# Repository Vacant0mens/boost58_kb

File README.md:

# boost58_kb
 
This layout was given this name because its shape looks similar to the boost arrows in racetrack video games.

# Introduction
I designed this board because I couldn't find any options that fit my requirements for a custom key board, which were:
1. completely reversible circuit board (for a split keyboard)
2. two-way UART communication between the two halves
3. compatible with Kailh Choch v2 switches (with v1 backward compatability)
4. hotswap switch sockets
5. staggered column layout (including a stagger for the outer-pinky column, and inner-index column)
6. 4 finger rows, plus only one thumb row
7. per-key and underglow RGB lights
8. anti-ghosting diodes
9.  promicro-style MCU
10. at least 1 rotary encoder per-side
11. reset button
12. power switch (optional)

I designed this with the intention of making it my dream keyboard, but also available and accessible to others. I am open to suggestions and PR's.

# Build Progress

## v0.2
### Top Layout v0.2

## v0.1

### Original Top Layout

# Thanks
Thanks to:
[ergogen](https://github.com/ergogen/ergogen) for the base software to be able to create this.
[ceoloide](https://github.com/ceoloide/ergogen-footprints) for the footprints and examples
[benvallack](https://github.com/benvallack) for the inspiration that started my custom keyboard journey and the `promicro_pretty` footprint (it's amazing).

# Buy Me a Coffee
[@Vacant0mens](https://buymeacoffee.com/vacan0mens)

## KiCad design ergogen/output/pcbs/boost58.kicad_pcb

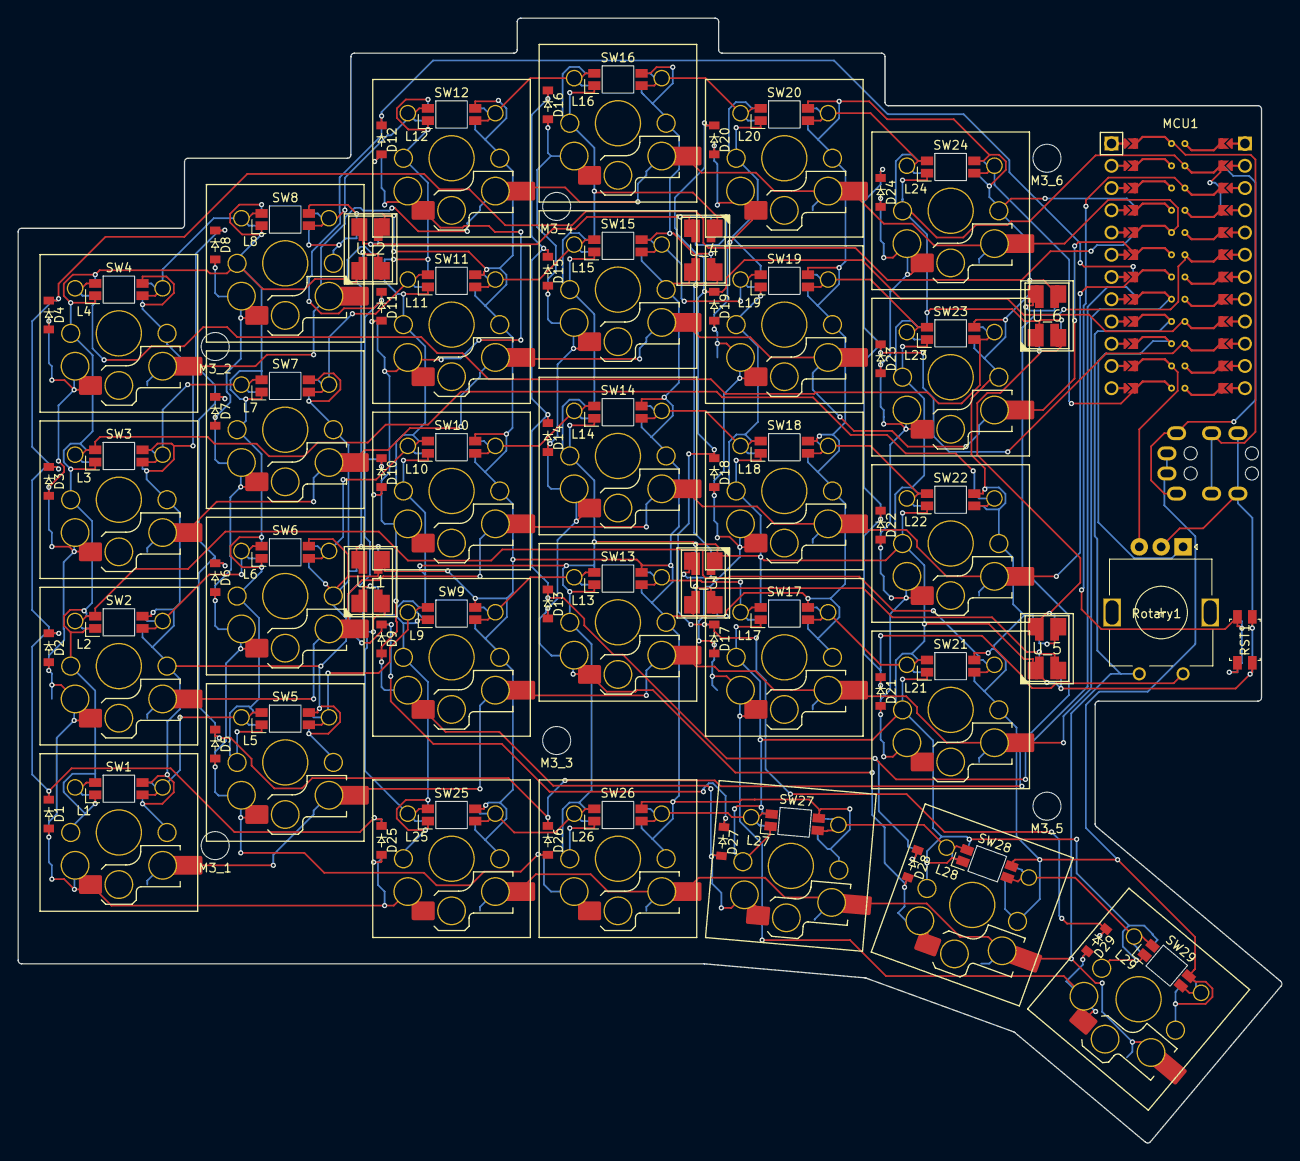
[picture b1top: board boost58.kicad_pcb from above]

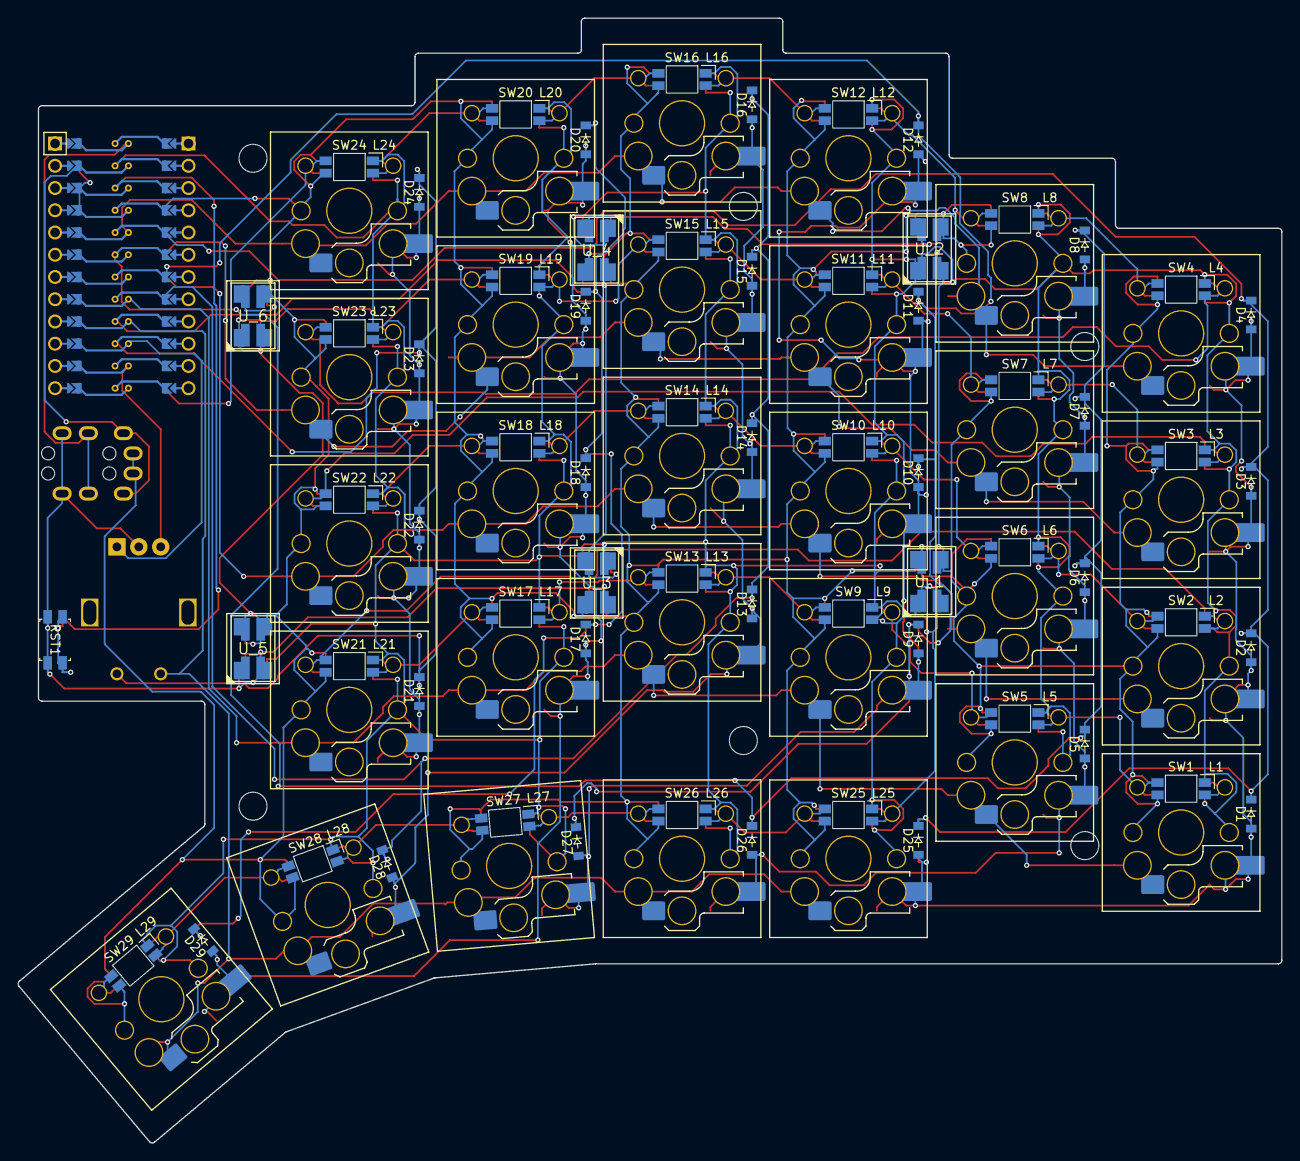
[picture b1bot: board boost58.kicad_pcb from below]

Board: 2 copper layers, 144.3 x 128.5 mm, 103 parts (87 on the bottom side), 59 nets.

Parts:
D1, D2, D3, D4, D5, D6, D7, D8, D9, D10, D11, D12, D13, D14, D15, D16, D17, D18, D19, D20, D21, D22, D23, D24, D25, D26, D27, D28, D29: ${REFERENCE}; diode_tht_sod123
L1, L2, L3, L4, L5, L6, L7, L8, L9, L10, L11, L12, L13, L14, L15, L16, L17, L18, L19, L20, L21, L22, L23, L24, L25, L26, L27, L28, L29: ${REFERENCE}; led_SK6812mini-e (per-key, reversible)
M3_1, M3_2, M3_3, M3_4, M3_5, M3_6: mounting_hole_npth
MCU1: ProMicro
RST1: reset_switch_smd_side
Rotary1: rotary_encoder
SW1, SW2, SW3, SW4, SW5, SW6, SW7, SW8, SW9, SW10, SW11, SW12, SW13, SW14, SW15, SW16, SW17, SW18, SW19, SW20, SW21, SW22, SW23, SW24, SW25, SW26, SW27, SW28, SW29: ${REFERENCE}; switch_choc_v1_v2
TRRS1: TRRS-PJ-320A-dual
U_1, U_2, U_3, U_4, U_5, U_6: ${REFERENCE}; WS2812B

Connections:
DP14: D21.2, D22.2, D23.2, D24.2, SW21.2, SW22.2, SW23.2, SW24.2
DP15: D17.2, D18.2, D19.2, D20.2, D29.2, SW17.2, SW18.2, SW19.2, SW20.2, SW29.2
DP18: D13.2, D14.2, D15.2, D16.2, D28.2, SW13.2, SW14.2, SW15.2, SW16.2, SW28.2
DP19: D9.2, D10.2, D11.2, D12.2, D27.2, SW9.2, SW10.2, SW11.2, SW12.2, SW27.2
DP20: D5.2, D6.2, D7.2, D8.2, D26.2, SW5.2, SW6.2, SW7.2, SW8.2, SW26.2
DP21: D1.2, D2.2, D3.2, D4.2, D25.2, SW1.2, SW2.2, SW3.2, SW4.2, SW25.2
GND: L1.3, L2.3, L3.3, L4.3, L5.3, L6.3, L7.3, L8.3, L9.3, L10.3, L11.3, L12.3, L13.3, L14.3, L15.3, L16.3, L17.3, L18.3, L19.3, L20.3, L21.3, L22.3, L23.3, L24.3, L25.3, L26.3, L27.3, L28.3, L29.3, MCU1.2, MCU1.21, MCU1.22, RST1.1, RST1.3, Rotary1.C, TRRS1.4, U_1.3, U_1.4, U_1.33, U_1.44, U_2.3, U_2.4, U_2.33, U_2.44, U_3.3, U_3.4, U_3.33, U_3.44, U_4.3, U_4.4, U_4.33, U_4.44, U_5.3, U_5.4, U_5.33, U_5.44, U_6.3, U_6.4, U_6.33, U_6.44
P0: MCU1.23, TRRS1.2
P1: MCU1.24, TRRS1.3
P2: MCU1.20, SW4.1, SW8.1, SW12.1, SW16.1, SW20.1, SW24.1
P3: MCU1.19, SW3.1, SW7.1, SW11.1, SW15.1, SW19.1, SW23.1
P4: MCU1.18, SW2.1, SW6.1, SW10.1, SW14.1, SW18.1, SW22.1
P5: MCU1.17, SW1.1, SW5.1, SW9.1, SW13.1, SW17.1, SW21.1
P6: MCU1.16, Rotary1.2, SW25.1, SW26.1, SW27.1, SW28.1, SW29.1
P7: MCU1.15, Rotary1.A
P8: MCU1.14, Rotary1.B
P9: L24.2, MCU1.13
P14: D21.1, D22.1, D23.1, D24.1, MCU1.10, Rotary1.1
P15: D17.1, D18.1, D19.1, D20.1, D29.1, MCU1.9
P18: D13.1, D14.1, D15.1, D16.1, D28.1, MCU1.8
P19: D9.1, D10.1, D11.1, D12.1, D27.1, MCU1.7
P20: D5.1, D6.1, D7.1, D8.1, D26.1, MCU1.6
P21: D1.1, D2.1, D3.1, D4.1, D25.1, MCU1.5
RST: MCU1.3, RST1.2, RST1.4
VCC: L1.1, L2.1, L3.1, L4.1, L5.1, L6.1, L7.1, L8.1, L9.1, L10.1, L11.1, L12.1, L13.1, L14.1, L15.1, L16.1, L17.1, L18.1, L19.1, L20.1, L21.1, L22.1, L23.1, L24.1, L25.1, L26.1, L27.1, L28.1, L29.1, MCU1.4, TRRS1.1, U_1.1, U_1.2, U_1.11, U_1.22, U_2.1, U_2.2, U_2.11, U_2.22, U_3.1, U_3.2, U_3.11, U_3.22, U_4.1, U_4.2, U_4.11, U_4.22, U_5.1, U_5.2, U_5.11, U_5.22, U_6.1, U_6.2, U_6.11, U_6.22
r0c1: L25.4, U_1.3, U_1.4, U_1.33, U_1.44
r0c2: L25.2, L26.4
r0c3: L26.2, L27.4
r0c4: L27.2, L28.4
r0c5: L28.2, L29.4
r1c1: L1.2, L5.4
r1c2: L5.2, L9.4
r1c3: L9.2, L13.4
r1c4: L13.2, L17.4
r1c5: L17.2, L21.4
r2c0: L2.4, L21.2
r2c1: L2.2, L6.4
r2c2: L6.2, L10.4
r2c3: L10.2, L14.4
r2c4: L14.2, L18.4
r2c5: L18.2, L22.4
r3c0: L3.4, L22.2
r3c1: L3.2, L7.4
r3c2: L7.2, L11.4
r3c3: L11.2, L15.4
r3c4: L15.2, L19.4
r3c5: L19.2, L23.4
r4c0: L4.4, L23.2
r4c1: L4.2, L8.4
r4c2: L8.2, L12.4
r4c3: L12.2, L16.4
r4c4: L16.2, L20.4
r4c5: L20.2, L24.4
u01: U_1.1, U_1.2, U_1.11, U_1.22, U_2.3, U_2.4, U_2.33, U_2.44
u02: U_2.1, U_2.2, U_2.11, U_2.22, U_4.3, U_4.4, U_4.33, U_4.44
u03: U_3.3, U_3.4, U_3.33, U_3.44, U_4.1, U_4.2, U_4.11, U_4.22
u04: U_3.1, U_3.2, U_3.11, U_3.22, U_5.3, U_5.4, U_5.33, U_5.44
u05: U_5.1, U_5.2, U_5.11, U_5.22, U_6.3, U_6.4, U_6.33, U_6.44
u06: U_6.1, U_6.2, U_6.11, U_6.22

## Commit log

2024-08-11 Initialized repo with Readme
2024-08-11 created ergogen config yaml
2024-08-11 pulled and modified footprints from ceoloide's footprints repo (PR incoming later)
2024-08-11 generated KiCad PCB's and outlines with ergogen
2024-08-11 autorouted and imported session to PCB
2024-08-11 exported STEP files for bottom, top, and spacer plates, and converted them to STL's for printing
2024-08-11 generated gerber and drill files (and put them in zip files for later use)
2024-08-11 updated ergogen config to have correct name in output files
2024-08-11 added picture of layout
2024-08-11 renamed files to correct name instead of generic/prototype name
2024-08-17 forgot to update the name when adding meta section
2024-08-20 reduced binding around inner_home key
2024-08-20 removed commented lines, refactored outline references to short syntax, made panel and keycap_outline internal-only
2024-08-20 removed PCB plates in favor of using the outlines as sketches in Fusion to make the case
2024-08-20 added keycap outlines to pcb silkscreens
2024-08-20 added a wall outline for the wall of the bottom case
2024-08-20 added material around the screw holes to support PCB
2024-08-20 increased _switch_spacer_cutouts size for better printability
2024-08-20 changed screw posts to be bigger, for heat-set threaded inserts
2024-08-20 changed size of top_plate cutout for MCU and Rotary Encoder
2024-08-20 created v0.1 zip file - main PCB has been made from these files
2024-08-20 removed excess outline and pcb files (already removed from config.yml)
2024-08-20 re-generated files for drawings (to make a new case in Fusion)
2024-08-20 un-did changes to top-plate cutout and binding on inner home key (will be part of v0.2 branch)
2024-08-20 reduced binding around inner_home and moved PowerSwitch to make pcb and case more streamlined
2024-08-20 moved screw holes and LED's for better placement with heat insert threads and bigger notch above thumb_inner
2024-08-20 re-generated PCB and drawings (will run auto-trace later)
2024-08-20 moved power switch back to match v0.1 until v0.2 is ready for PCB creation and new case
2024-08-20 added polygon to MCU/Rotary cutout so that it looks nicer
2024-08-20 added STL's for bottom case and top/key plate
2024-08-20 re-generated drawings
2024-08-20 removed excess step files
2024-08-24 added kmk firmware folder to .gitignore
2024-08-24 added cutouts in bottom case for buttons and USB port
2024-08-24 made bottom case wall slightly larger to compensate for PCB tolerances
2024-08-24 removed keycap outline drawing file and re-generated all outlines
2024-08-24 created new STL's with Fusion from drawing files
2024-08-24 added lib folder (for kmk) to .gitignore
2024-08-24 added WorkInProgress main.py and kb_boost58.py files for KMK
2024-08-24 added slight updates to footprints for contributing to ceoloide/ergogen-footprints
2024-08-24 changed polygon cutout to line up better with thumb_inner key outline
2024-08-24 moved per-key diodes to keep clear of hotswap sockets
2024-08-24 moved power switch to be above reset switch to accommodate bigger space above thumb_inner key
2024-08-24 added panel_wall to PCB for reference, reduced fillet so it doesn't have sharp corners on the cutouts
2024-08-24 re-generated drawings and PCB
2024-08-24 updated sk6812 footprint to have the silkscreen labels not be printed backwards
2024-08-24 moved/resized trrs_pwr_rst cutout to accommodate power switch move
2024-08-24 regenerated drawings and PCB
2024-08-24 added fillet to PCB corners
2024-08-24 moved panel wall drawing to User.Drawings instead of Edge.Cuts (default)
2024-08-24 re-generated PCB
2024-08-26 added vias to smd diodes (when include_tht == false) for easier routing
2024-08-26 added second vias to sk6812-e for easier routing
2024-08-26 added optional v1 stabilizer PTH's to reduce vias when routing, if needed
2024-08-26 added footprint for surface-mount/"pinless" Sparkfun Promicro Qwiic. I thought it might make reversibility of the whole board easier, and it's kinda cool
2024-08-26 removed excess top plate cutout drawing on PCB - got DRC warnings for silkscreen cut off by edge
2024-08-26 added reversible surface-mount Sparkfun Promicro Qwiic to PCB
2024-08-26 removed PTH from diodes to make room for routing
2024-08-26 updated nets for Sparkfun Promicro Qwiic
2024-08-26 added v1 and v2 stabilizer nets and PTHoles for all stabilizers to help with routing
2024-08-26 made cutout slightly wider
2024-08-26 removed second vias from sk6812-e -- not needed with PTH stabs
2024-08-26 changed traces for sk6812-e to match default KiCad trace width
2024-08-26 re-generated PCB, and re-ran FreeRouting
2024-09-01 made the led_WS2812B footprint actually reversible with the pads on the correct sides and the silkscreens facing the right way
2024-09-01 moved key diode to the left side of the key (or right side of the key if it's the right-hand board) for easier routing
2024-09-01 reduced binding along the top for better uniformity
2024-09-01 corrected thumb-key nets to reduce unused columns
2024-09-01 updated key diode shift values to use the presets
2024-09-01 corrected rotary nets to match the changes with the thumb key nets
2024-09-01 cleaned up underglow LED's to utilize the reversible setting rather than making each one on each side
2024-09-01 added presets for MX switches
2024-09-01 added matrix_mx and thumb_mx to extend/modify the current zones to use MX measurements
2024-09-01 added _panel_mx and _keycap_outline_mx to config
2024-09-01 added boost58_mx PCB that extends boost58 PCB (testing)
2024-09-01 generated boost58_mx kicad_pcb and ran initial traces with FreeRouting
2024-09-01 added switch_mx footprint, modified from ergogen's footprints
2024-09-01 added promicro_pretty footprint by @benvallack
2024-09-01 adjusted led_WS2812B silkscreens to not sit under the pads
2024-09-01 increased default binding to help with routing around the edge of the PCB
2024-09-01 fixed bindings and key placements after shortening the key spread
2024-09-01 changed keycap size and key spread to be more compact and accurate
2024-09-01 shifted non-key components and made components area slightly bigger to make the case look nicer and give space for routing
2024-09-01 removed polygon cutout from top plate. no longer needed with component readjustments; also resized rectangle top plate cutout to match component shifts
2024-09-01 changed to use @benvallack's promicro_pretty footprint, updated pin/net names
2024-09-01 re-generated pcb's and outlines
2024-09-01 added @benvallack to thanks section in readme
2024-09-01 broke up thanks in readme to one-per-line
2024-09-01 added starts for bento travel case
2024-09-01 added pin to account for extra column in matrix+thumb zones
2024-09-01 added extra unused keys for extra columns in matrix+thumb zones
2024-09-01 re-generated pcb and ran FreeRouting
2024-09-01 changed numbers on underglow light names in yaml to follow the circuit board convention
2024-09-02 flipped routes for underglow to make routing shorter and hopefully easier
2024-09-02 re-generated PCB and applied FreeRouting
2024-09-02 created Tent Wedge and Wrist Rest models in Fusion based on drawings
2024-09-02 exported STL and drawings from Fusion for later work with the case add-ons
2024-09-23 added a wedge and wrist rest to current case design
2024-09-23 redesigned case to be unibody with wrist rest built in
2024-09-23 combined both case designs; lower tilt angle, built-in wedge, but with a detachable wrist rest
2024-09-23 switched space and layer-2 key in key layout
2024-09-23 added spacing to make the board outline more uniform
2024-09-23 shortened the stagger for the outer-pinky column; it was a little too low.
2024-09-23 removed power switch. No plans to make this board wireless or battery-powered
2024-11-02 changed column and row labels/numbers to be easier to read (for humans)
2024-11-02 added LED Pin variable
2024-11-02 moved diode slightly
2024-11-02 moved screw holes so that only one or two keycaps need to be removed to get access to each screw
2024-11-02 used variable for switch socket footprint
2024-11-02 changed to use variables for per-key LED's, added parameter to move ref/label of key diode
2024-11-02 renamed and moved (slightly) the underglow LED's
2024-11-02 renamed pins for TRRS to follow convention
2024-11-02 switched UART pins, turned off uart_flip for Right
2024-11-02 Added pinout info sheet for SparkFun ProMicro RP2040, for reference
2024-11-02 created final release/archive of v0.1 for historical purposes as v0.2 gets closer to complete
2024-11-02 moved stl files from v0.1 to their own folder
2024-11-02 added top plate STL for v0.2
2024-11-02 removed excess rules file for autotrace
2024-11-02 re-generated circuit board and outlines, ran autotrace -- v0.2 almost ready!
2024-11-02 re-generated gerber and drill files
2024-11-02 removed old drill and gerber files from spacer and top plates (not needed)
2024-11-02 changed some settings for gerber output
2024-11-06 generated gerbers and drills for JLCPCB
2024-11-07 Added KiCad v8 properties for easier generation and handling of BOM and placement files
2024-11-07 added picture of v0.1 build
2024-11-07 moved images to their own folder
2024-11-07 added images to main readme
2024-11-07 added layout image for v0.2
2024-11-07 added KiCad v8 properties for key LED's and key diodes
2024-11-11 Moved v0.1 case files to separate folders
2024-11-11 Created new printable v0.2 case files
2024-11-11 autoformatted config.yml by vscode
2024-11-11 reordered rgb matrix to fit schema
2024-11-11 updated pins to match schematic, removed split_side arguments to enable EE Hands
2024-11-11 updated key layout for v0.2 schematic
2024-11-11 Fixed backwards per-key LED layout/circuit
2024-11-11 fixed disconnected thumb-key LED's
2024-11-30 added RGB extension
2024-11-30 updated number of lights for RGB and updated settings for RGB instead of RGB_Matrix
2024-11-30 updated rotary encoder settings for new version of circuit
2024-11-30 fixed pins and config for UART connection
2024-11-30 added cutouts for the TRRS and Reset specifically, rather than one big cutout
2024-11-30 disabled OneShot and added logs (logs helped find that OneShot was broken in KMK, for now).
2024-11-30 added Layer 3 in key layout
2024-11-30 added STL's for case (so far)
2024-11-30 added custom RGB function, still needs work.
2024-11-30 implemented custom RGB extention, removed unnecessary code from kb_boost58, and rearranged the lines to be grouped nicely
2024-11-30 moved colors to custom_rgb file, disabled debug
2024-11-30 added debug log capability to custom_rgb
2024-11-30 added inheriting the AnimationModes class for custom_rgb
2024-11-30 updated LED_COUNT and CHANCE_OF_NEW_LIGHT, added DIM_STEP, MULTIPLIER, and pre-calculated POSSIBLE_LIGHTS
2024-11-30 removed *args from init; it was halting super().__init__() for some reason
2024-11-30 added in-memory tracking for LED status/color (KMK doesn't have a 'get' function for it)
2024-11-30 changed random.getrandbits for random.choice for easier reading and troubleshooting
2024-11-30 added custom animate function to add twinkle as an option
2024-11-30 added MO(3) to left half instead of an extra Ctrl button
2024-11-30 added third layer to encoders
2024-11-30 made each half able to independently change RGB light modes; KMK doesn't communicate that between the halves
